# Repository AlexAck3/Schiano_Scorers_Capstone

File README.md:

# Capstone to make Dr. S Proud

Click [here](https://pennstateoffice365-my.sharepoint.com/:w:/r/personal/ama8308_psu_edu/Documents/Capstone%20Ideas.docx?d=wde995918626b463aa603d03eb18d9986&csf=1&web=1&e=Yd5YqW) to see the ideation doc

## Pizza Oven Competition
[Ooni Volt 2](https://ooni.com/products/ooni-volt-2)\
Dimensions: 545 x 442 x 263 mm

[Breville Pizzaiolo](https://www.breville.com/en-us/product/bpz820?sku=BPZ820BSS1BUC1)\
Dimensions: 18.1" x 18.5" x 10.6"

## Goals
1. Have a working oven that can cook pizza
2. Oven temp stability within 10F of set temp
3. Reach 850F+ for Neapolitan pizza
4. Accurate sensing of pizza completion (within 5% of proper cook)

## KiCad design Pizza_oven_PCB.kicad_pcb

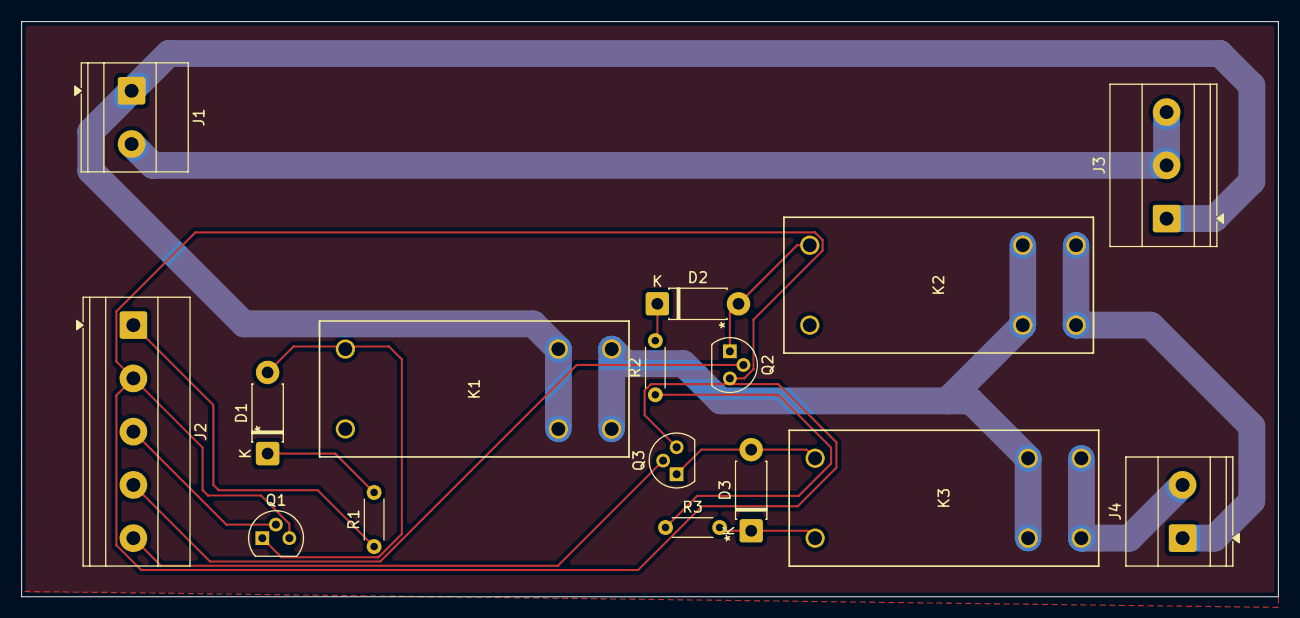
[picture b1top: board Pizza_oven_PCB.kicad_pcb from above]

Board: 2 copper layers, 118.0 x 54.0 mm, 16 parts (0 on the bottom side), 16 nets.

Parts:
D1, D2, D3: D; D_DO-41_SOD81_P7.62mm_Horizontal
J1, J4: Screw_Terminal_01x02; TerminalBlock_Phoenix_MKDS-1,5-2_1x02_P5.00mm_Horizontal
J2: Screw_Terminal_01x05; TerminalBlock_Phoenix_MKDS-1,5-5_1x05_P5.00mm_Horizontal
J3: Screw_Terminal_01x03; TerminalBlock_Phoenix_MKDS-1,5-3_1x03_P5.00mm_Horizontal
K1, K2, K3: G2RL-1A-E DC24; RELAY_G2RL-1A-E DC5_OMR
Q1, Q2, Q3: NPN; TO-92L
R1, R2, R3: R_US; R_Axial_DIN0204_L3.6mm_D1.6mm_P5.08mm_Horizontal

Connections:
/BOTTOM COIL: J4.2, K3.4, K3.5
/DIGITAL POWER: J2.1, R1.1, R2.1, R3.1
/DIN 1: J2.3, Q1.2 (B)
/DIN 2: J2.4, Q2.2 (B)
/DIN 3: J2.5, Q3.2 (B)
/MAIN IN: J1.1, J3.1, K1.3, K1.6
/NEUTRAL IN: J1.2, J3.2, J3.3
/TOP COIL: J4.1, K2.4, K2.5
GND: J2.2, Q1.3 (E), Q2.3 (E), Q3.3 (E)
unnamed: D1.2 (A), K1.8, Q1.1 (C)
unnamed: D1.1 (K), K1.1, R1.2
unnamed: D2.2 (A), K2.8, Q2.1 (C)
unnamed: D2.1 (K), K2.1, R2.2
unnamed: D3.2 (A), K3.8, Q3.1 (C)
unnamed: D3.1 (K), K3.1, R3.2
unnamed: K1.4, K1.5, K2.3, K2.6, K3.3, K3.6

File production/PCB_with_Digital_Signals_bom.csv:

Designator,Footprint,Quantity,Value,LCSC Part #
"D1, D2, D3",D_DO-41_SOD81_P7.62mm_Horizontal,3,D,
"J1, J4","TerminalBlock_Phoenix_MKDS-1,5-2_1x02_P5.00mm_Horizontal",2,Screw_Terminal_01x02,
J2,"TerminalBlock_Phoenix_MKDS-1,5-5_1x05_P5.00mm_Horizontal",1,Screw_Terminal_01x05,
J3,"TerminalBlock_Phoenix_MKDS-1,5-3_1x03_P5.00mm_Horizontal",1,Screw_Terminal_01x03,
"K1, K2, K3",RELAY_G2RL-1A-E DC5_OMR,3,G2RL-1A-E DC24,
"Q1, Q2, Q3",TO-92L,3,NPN,
"R1, R2, R3",R_Axial_DIN0204_L3.6mm_D1.6mm_P5.08mm_Horizontal,3,R_US,

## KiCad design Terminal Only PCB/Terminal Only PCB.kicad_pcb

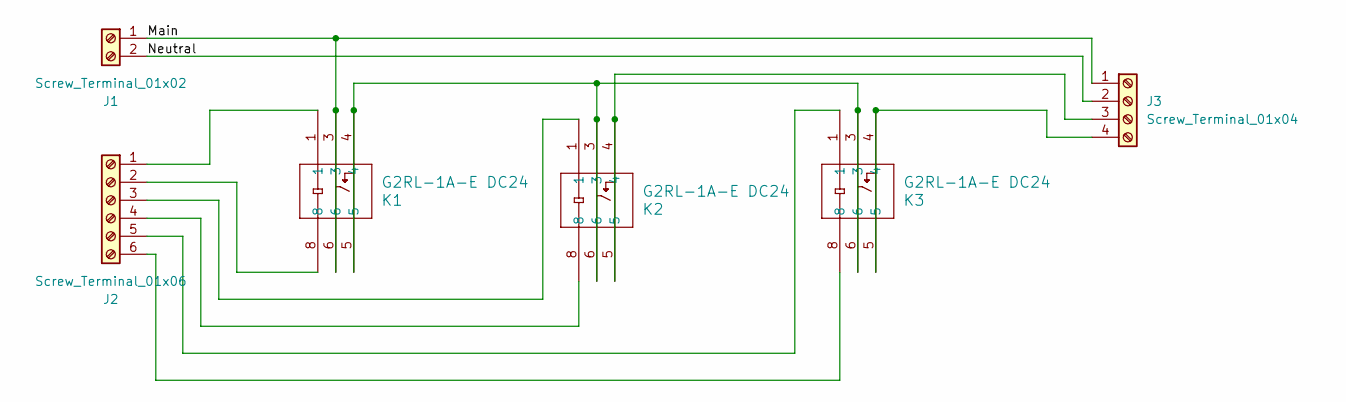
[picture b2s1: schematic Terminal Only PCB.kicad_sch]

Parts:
J1: Screw_Terminal_01x02; TerminalBlock_Phoenix_MKDS-1,5-2-5.08_1x02_P5.08mm_Horizont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
J2: Screw_Terminal_01x06; TerminalBlock_Phoenix_MKDS-1,5-6-5.08_1x06_P5.08mm_Horizont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
J3: Screw_Terminal_01x04; TerminalBlock_Phoenix_MKDS-1,5-4-5.08_1x04_P5.08mm_Horizont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
K1, K2, K3: G2RL-1A-E DC24; RELAY_G2RL-1A-E DC5_OMR

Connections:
/Main: J1.1, J3.1, K1.3, K1.6
/Neutral: J1.2, J3.2
unnamed: J2.1, K1.1
unnamed: J2.2, K1.8
unnamed: J2.3, K2.1
unnamed: J2.4, K2.8
unnamed: J2.5, K3.1
unnamed: J2.6, K3.8
unnamed: J3.3, K2.4, K2.5
unnamed: J3.4, K3.4, K3.5
unnamed: K1.4, K1.5, K2.3, K2.6, K3.3, K3.6

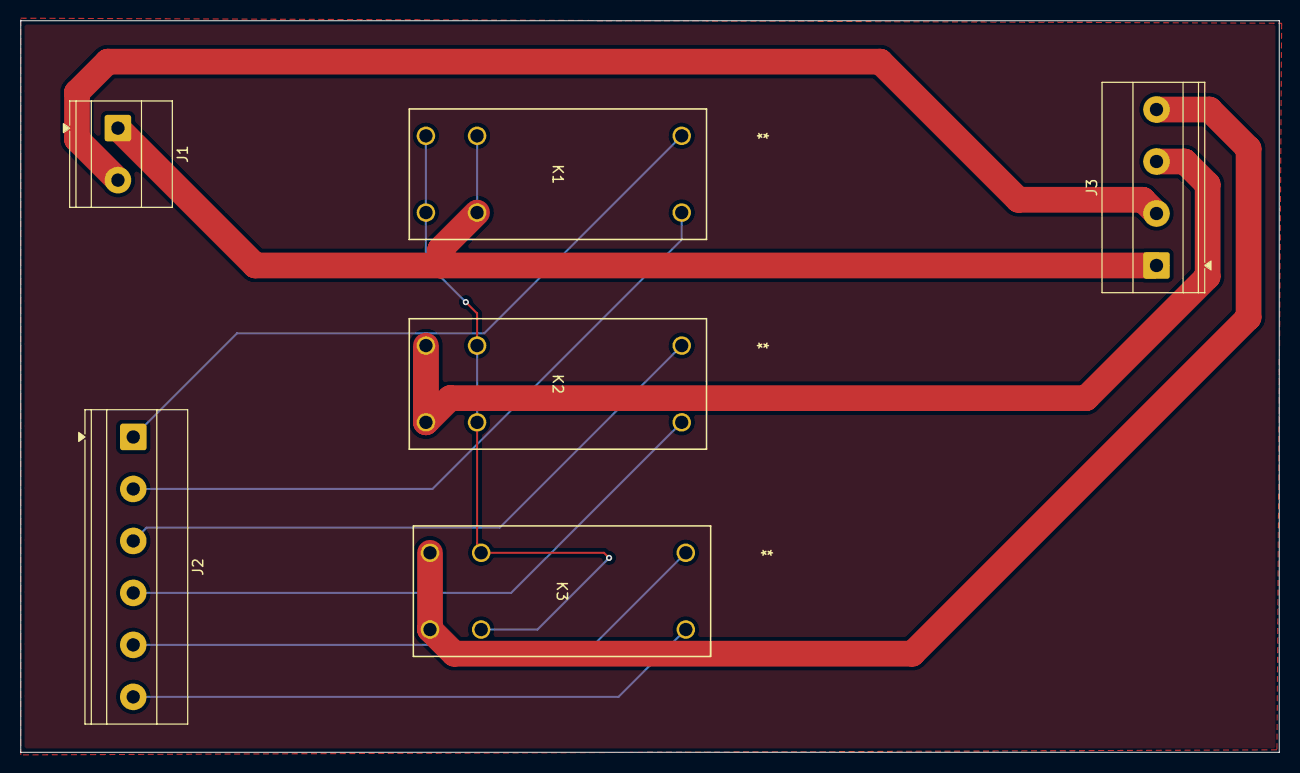
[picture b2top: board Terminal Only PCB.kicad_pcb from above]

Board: 2 copper layers, 123.0 x 71.5 mm, 6 parts (0 on the bottom side), 11 nets.

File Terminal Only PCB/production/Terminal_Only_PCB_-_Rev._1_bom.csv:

Designator,Footprint,Quantity,Value,LCSC Part #
J1,"TerminalBlock_Phoenix_MKDS-1,5-2-5.08_1x02_P5.08mm_Horizontal",1,Screw_Terminal_01x02,
J2,"TerminalBlock_Phoenix_MKDS-1,5-6-5.08_1x06_P5.08mm_Horizontal",1,Screw_Terminal_01x06,
J3,"TerminalBlock_Phoenix_MKDS-1,5-4-5.08_1x04_P5.08mm_Horizontal",1,Screw_Terminal_01x04,
"K1, K2, K3",RELAY_G2RL-1A-E DC5_OMR,3,G2RL-1A-E DC24,
